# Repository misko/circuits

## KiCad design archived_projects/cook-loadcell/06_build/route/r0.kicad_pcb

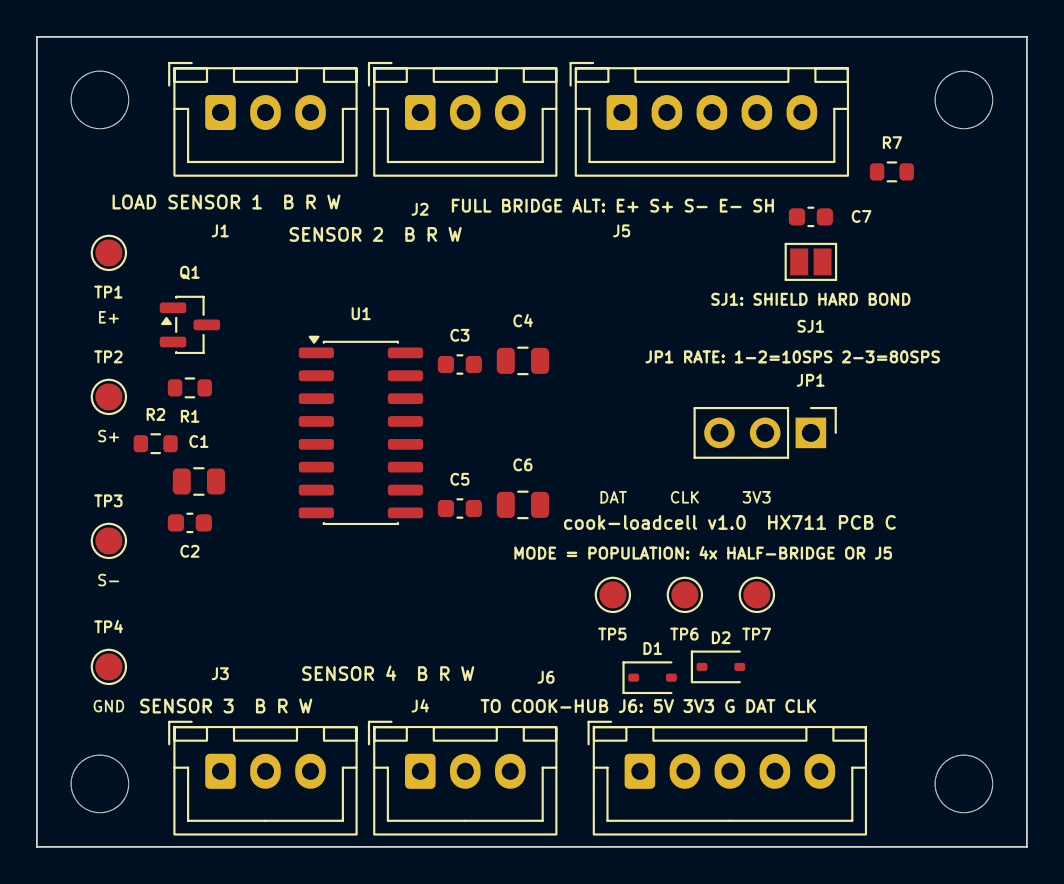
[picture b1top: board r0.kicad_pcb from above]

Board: 2 copper layers, 55.0 x 45.0 mm, 33 parts (0 on the bottom side), 16 nets, no tracks yet.

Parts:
C1: 10u E+; C_0805_2012Metric
C2: 100n E+; C_0603_1608Metric
C3: 100n DVDD; C_0603_1608Metric
C4: 10u 3V3; C_0805_2012Metric
C5: 100n VSUP; C_0603_1608Metric
C6: 10u 5V; C_0805_2012Metric
C7: 100n shield bond; C_0603_1608Metric
D1, D2: PESD5V0S1BA; D_SOD-323
H1, H2, H3, H4: MountingHole_3.2mm_M3
J1: SENSOR 1 B/R/W; JST_XH_B3B-XH-A_1x03_P2.50mm_Vertical
J2: SENSOR 2 B/R/W; JST_XH_B3B-XH-A_1x03_P2.50mm_Vertical
J3: SENSOR 3 B/R/W; JST_XH_B3B-XH-A_1x03_P2.50mm_Vertical
J4: SENSOR 4 B/R/W; JST_XH_B3B-XH-A_1x03_P2.50mm_Vertical
J5: FULL BRIDGE ALT; JST_XH_B5B-XH-A_1x05_P2.50mm_Vertical
J6: TO HUB J6; JST_XH_B5B-XH-A_1x05_P2.50mm_Vertical
JP1: RATE 1-2=10SPS 2-3=80; PinHeader_1x03_P2.54mm_Vertical
Q1: S8550; SOT-23
R1: 20k 1% AVDD-VFB; R_0603_1608Metric
R2: 8.2k 1% VFB-GND; R_0603_1608Metric
R7: 100R shield bond; R_0603_1608Metric
SJ1: SH hard bond DNP; SolderJumper-2_P1.3mm_Open_Pad1.0x1.5mm
TP1: TP E+; TestPoint_Pad_D1.5mm
TP2: TP S+; TestPoint_Pad_D1.5mm
TP3: TP S-; TestPoint_Pad_D1.5mm
TP4: TP GND; TestPoint_Pad_D1.5mm
TP5: TP DAT; TestPoint_Pad_D1.5mm
TP6: TP CLK; TestPoint_Pad_D1.5mm
TP7: TP 3V3; TestPoint_Pad_D1.5mm
U1: HX711; SOIC-16_3.9x9.9mm_P1.27mm

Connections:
3V3: C3.1, C4.1, J6.2, JP1.3, TP7.1, U1.16
5V: C5.1, C6.1, J6.1, Q1.2, U1.1
AVDD_FB: R1.2, R2.1, U1.4
BASE: Q1.1, U1.2
CLK: D2.1, J6.5, TP6.1, U1.11
DAT: D1.1, J6.4, TP5.1, U1.12
E_PLUS: C1.1, C2.1, J1.2, J5.1, Q1.3, R1.1, TP1.1, U1.3
GND: C1.2, C2.2, C3.2, C4.2, C5.2, C6.2, C7.2, D1.2, D2.2, J3.2, J5.4, J6.3, JP1.1, R2.2, R7.2, SJ1.2, TP4.1, U1.5, U1.9, U1.10, U1.14
RATE_SEL: JP1.2, U1.15
RING_12: J1.3, J2.1
RING_23: J2.3, J3.1
RING_34: J3.3, J4.1
RING_41: J1.1, J4.3
SH: C7.1, J5.5, R7.1, SJ1.1
S_MINUS: J4.2, J5.3, TP3.1, U1.7
S_PLUS: J2.2, J5.2, TP2.1, U1.8

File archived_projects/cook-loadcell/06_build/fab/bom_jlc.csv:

Comment,Designator,Footprint,MPN,LCSC
100R shield bond,R7,R_0603_1608Metric,,C22775
100n,"C2,C3,C5,C7",C_0603_1608Metric,,C14663
10u,"C1,C4,C6",C_0805_2012Metric,,C15850
20k 1% AVDD-VFB,R1,R_0603_1608Metric,,C4184
8.2k 1% VFB-GND,R2,R_0603_1608Metric,,C25981
FULL BRIDGE ALT / TO HUB J6,"J5,J6",JST_XH_B5B-XH-A_1x05_P2.50mm_Vertical,B5B-XH-A(LF)(SN),C157991
HX711,U1,SOIC-16_3.9x9.9mm_P1.27mm,,C43656
PESD5V0S1BA,"D1,D2",D_SOD-323,PESD5V0S1BA,C5158048
RATE 1-2=10SPS 2-3=80,JP1,PinHeader_1x03_P2.54mm_Vertical,,
S8550,Q1,SOT-23,SS8550,C8542
SENSOR,"J1,J2,J3,J4",JST_XH_B3B-XH-A_1x03_P2.50mm_Vertical,,C144394

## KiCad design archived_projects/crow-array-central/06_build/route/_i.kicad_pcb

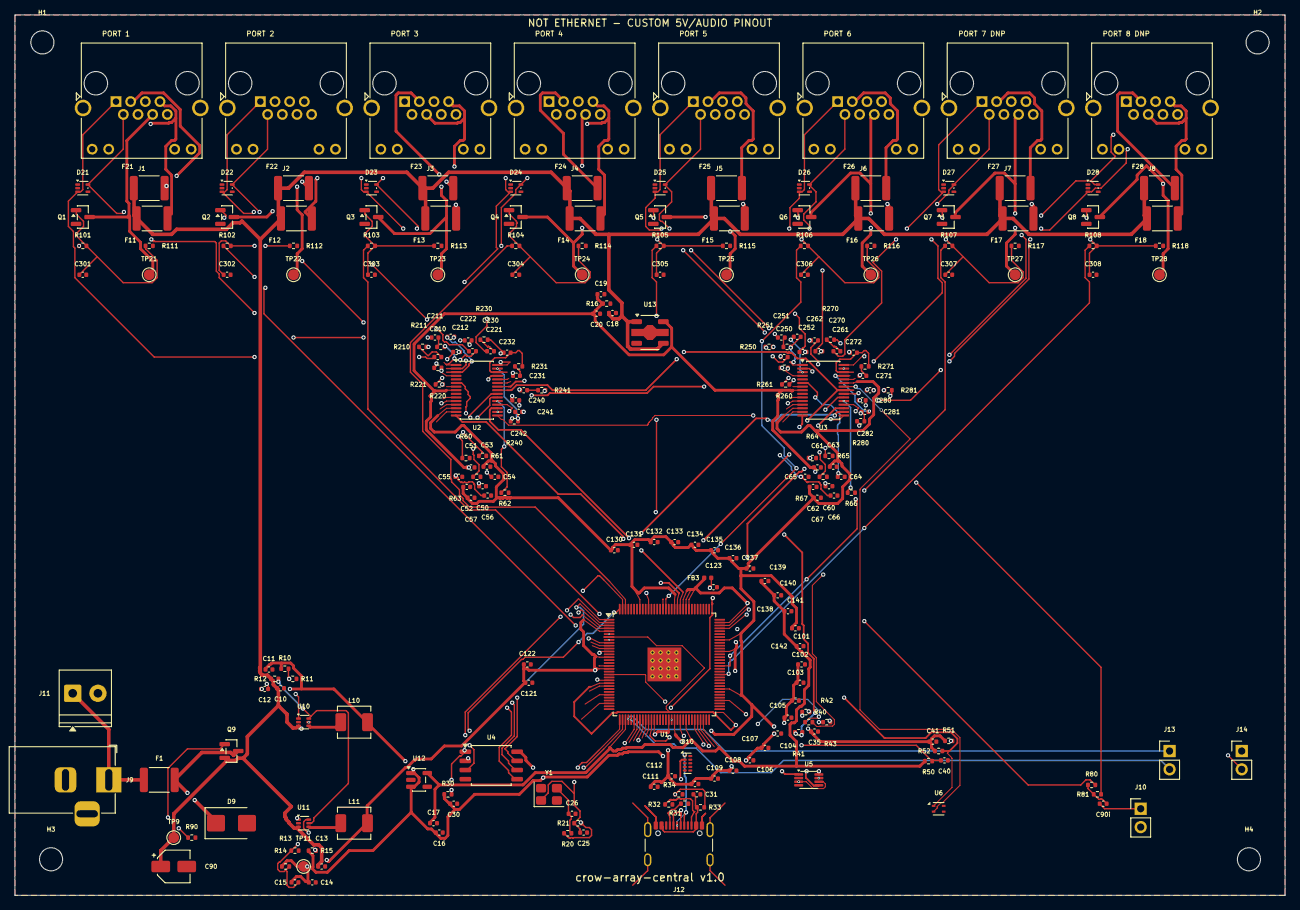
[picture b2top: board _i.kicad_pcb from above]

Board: 6 copper layers, 176.0 x 122.0 mm, 238 parts (0 on the bottom side), 151 nets.

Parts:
C10, C13, C18: 4u7 VIN; C_0402_1005Metric
C11, C136, C137: 10u 3V3; C_0402_1005Metric
C12: 100p FF; C_0402_1005Metric
C14: 22u 0V9; C_0402_1005Metric
C15: 560p FF; C_0402_1005Metric
C16: 1u VIN; C_0402_1005Metric
C17: 1u 1V8; C_0402_1005Metric
C19: 10u 3V3A; C_0402_1005Metric
C20: 100n 3V3A; C_0402_1005Metric
C25: 18p CL1; C_0402_1005Metric
C26: 18p CL2; C_0402_1005Metric
C30: 100n flash; C_0402_1005Metric
C31: 1u VBUS; C_0402_1005Metric
C35: 100n buf; C_0402_1005Metric
C40: 10n RST; C_0402_1005Metric
C41: 100n SHT; C_0402_1005Metric
C50: 4u7 AVDD_A; C_0402_1005Metric
C51: 100n AVDD_A; C_0402_1005Metric
C52: 4u7 DVDD_A; C_0402_1005Metric
C53: 100n DVDD_A; C_0402_1005Metric
C54: 2u2 VREF_A; C_0402_1005Metric
C55: 2u2 LDO_A; C_0402_1005Metric
C56: 100n LDO_A; C_0402_1005Metric
C57: 100n IOV_A; C_0402_1005Metric
C60: 4u7 AVDD_B; C_0402_1005Metric
C61: 100n AVDD_B; C_0402_1005Metric
C62: 4u7 DVDD_B; C_0402_1005Metric
C63: 100n DVDD_B; C_0402_1005Metric
C64: 2u2 VREF_B; C_0402_1005Metric
C65: 2u2 LDO_B; C_0402_1005Metric
C66: 100n LDO_B; C_0402_1005Metric
C67: 100n IOV_B; C_0402_1005Metric
C90: 100u 5V bulk; CP_Elec_4x5.4
C90i: 1u inj; C_0402_1005Metric
C101, C102, C103, C104, C105, C106, C107, C108, C109, C110, C111, C112: 100n VDD; C_0402_1005Metric
C121, C122: 10u VDD; C_0402_1005Metric
C123: 1u PLL; C_0402_1005Metric
C130, C131, C132, C133, C134, C135: 100n 3V3; C_0402_1005Metric
C138, C139: 100n 1V8; C_0402_1005Metric
C140: 10u 1V8; C_0402_1005Metric
C141: 100n USB33; C_0402_1005Metric
C142: 100n USB18; C_0402_1005Metric
C210: 1u cpl P1; C_0402_1005Metric
C211: 1u cpl N1; C_0402_1005Metric
C212: 1n diff 1; C_0402_1005Metric
C220: 1u cpl P2; C_0402_1005Metric
C221: 1u cpl N2; C_0402_1005Metric
C222: 1n diff 2; C_0402_1005Metric
C230: 1u cpl P3; C_0402_1005Metric
C231: 1u cpl N3; C_0402_1005Metric
C232: 1n diff 3; C_0402_1005Metric
C240: 1u cpl P4; C_0402_1005Metric
C241: 1u cpl N4; C_0402_1005Metric
C242: 1n diff 4; C_0402_1005Metric
C250: 1u cpl P5; C_0402_1005Metric
C251: 1u cpl N5; C_0402_1005Metric
C252: 1n diff 5; C_0402_1005Metric
C260: 1u cpl P6; C_0402_1005Metric
C261: 1u cpl N6; C_0402_1005Metric
C262: 1n diff 6; C_0402_1005Metric
C270: 1u cpl P7; C_0402_1005Metric
C271: 1u cpl N7; C_0402_1005Metric
C272: 1n diff 7; C_0402_1005Metric
C280: 1u cpl P8; C_0402_1005Metric
C281: 1u cpl N8; C_0402_1005Metric
C282: 1n diff 8; C_0402_1005Metric
C301: 4n7 gate 1; C_0402_1005Metric
C302: 4n7 gate 2; C_0402_1005Metric
C303: 4n7 gate 3; C_0402_1005Metric
C304: 4n7 gate 4; C_0402_1005Metric
C305: 4n7 gate 5; C_0402_1005Metric
C306: 4n7 gate 6; C_0402_1005Metric
C307: 4n7 gate 7; C_0402_1005Metric
C308: 4n7 gate 8; C_0402_1005Metric
D9: SMBJ5.0A TVS; D_SMB
D10: TPD4EUSB30; USON-10_2.5x1.0mm_P0.5mm
D21: TPD2E2U06 p1; SOT-553
D22: TPD2E2U06 p2; SOT-553
D23: TPD2E2U06 p3; SOT-553
D24: TPD2E2U06 p4; SOT-553
D25: TPD2E2U06 p5; SOT-553
D26: TPD2E2U06 p6; SOT-553
D27: TPD2E2U06 p7; SOT-553
D28: TPD2E2U06 p8; SOT-553
F1: 2A PTC; Fuse_1812_4532Metric
F11: PTC audio 1; Fuse_1812_4532Metric
F12: PTC audio 2; Fuse_1812_4532Metric
F13: PTC audio 3; Fuse_1812_4532Metric
F14: PTC audio 4; Fuse_1812_4532Metric
F15: PTC audio 5; Fuse_1812_4532Metric
F16: PTC audio 6; Fuse_1812_4532Metric
F17: PTC audio 7; Fuse_1812_4532Metric
F18: PTC audio 8; Fuse_1812_4532Metric
F21: PTC beep 1; Fuse_1812_4532Metric
F22: PTC beep 2; Fuse_1812_4532Metric
F23: PTC beep 3; Fuse_1812_4532Metric
F24: PTC beep 4; Fuse_1812_4532Metric
F25: PTC beep 5; Fuse_1812_4532Metric
F26: PTC beep 6; Fuse_1812_4532Metric
F27: PTC beep 7; Fuse_1812_4532Metric
F28: PTC beep 8; Fuse_1812_4532Metric
FB3: 600R PLL; L_0402_1005Metric
H1, H2, H3, H4: MountingHole_3.2mm_M3
J1, J2, J3, J4, J5, J6: RJHSE-5384; RJ45_Amphenol_RJHSE538X
J7, J8: RJHSE-5384 DNP; RJ45_Amphenol_RJHSE538X
J9: DC-005 5V IN; BarrelJack_Horizontal
J10: INJ IN; PinHeader_1x02_P2.54mm_Vertical
J11: 5V TERM DNP; TerminalBlock_Phoenix_PT-1,5-2-3.5-H_1x02_P3.50mm_Horizontal
J12: USB4105-GF-A; USB_C_Receptacle_GCT_USB4105-xx-A_16P_TopMnt_Horizontal
J13: xSYS DBG TDI/TDO; PinHeader_1x02_P2.54mm_Vertical
J14: xSYS DBG TMS/TCK; PinHeader_1x02_P2.54mm_Vertical
L10: 1u0 3V3; L_Sunlord_MWSA0402S
L11: 1u0 0V9; L_Sunlord_MWSA0402S
Q1: AO3400A beep 1; SOT-23
Q2: AO3400A beep 2; SOT-23
Q3: AO3400A beep 3; SOT-23
Q4: AO3400A beep 4; SOT-23
Q5: AO3400A beep 5; SOT-23
Q6: AO3400A beep 6; SOT-23
Q7: AO3400A beep 7; SOT-23
Q8: AO3400A beep 8; SOT-23
Q9: AO3401A revFET; SOT-23
R10: 68k FB1 hi; R_0402_1005Metric
R11: 15k FB1 lo; R_0402_1005Metric
R12: 10k PG1 pu; R_0402_1005Metric
R13: 10k FB2 hi; R_0402_1005Metric
R14: 20k FB2 lo; R_0402_1005Metric
R15: 10k PG2 pu; R_0402_1005Metric
R16: 4k7 bleed; R_0402_1005Metric
R20: 680R Rd; R_0402_1005Metric
R21: 1M Rf; R_0402_1005Metric
R30: 10k CS pu; R_0402_1005Metric
R31: 5k1 CC1 Rd; R_0402_1005Metric
R32: 5k1 CC2 Rd; R_0402_1005Metric
R33: 220k VBUS; R_0402_1005Metric
R34: 330k VBUS; R_0402_1005Metric
R40: 33R MCLK_A; R_0402_1005Metric
R41: 33R MCLK_B; R_0402_1005Metric
R42: 33R BCLK; R_0402_1005Metric
R43: 33R LRCK; R_0402_1005Metric
R50: 10k RST pu; R_0402_1005Metric
R51: 4k7 SCL pu; R_0402_1005Metric
R52: 4k7 SDA pu; R_0402_1005Metric
R60: 100k GP0_A; R_0402_1005Metric
R61: 100k GP1_A; R_0402_1005Metric
R62: 100k GP2_A; R_0402_1005Metric
R63: 100k GP3_A; R_0402_1005Metric
R64: 100k GP0_B; R_0402_1005Metric
R65: 100k GP1_B; R_0402_1005Metric
R66: 100k GP2_B; R_0402_1005Metric
R67: 100k GP3_B; R_0402_1005Metric
R80: 1k inj ch4; R_0402_1005Metric
R81: 1k inj ch8; R_0402_1005Metric
R90: 100k FET gate; R_0402_1005Metric
R101: 1k gate 1; R_0402_1005Metric
R102: 1k gate 2; R_0402_1005Metric
R103: 1k gate 3; R_0402_1005Metric
R104: 1k gate 4; R_0402_1005Metric
R105: 1k gate 5; R_0402_1005Metric
R106: 1k gate 6; R_0402_1005Metric
R107: 1k gate 7; R_0402_1005Metric
R108: 1k gate 8; R_0402_1005Metric
R111: 100k pd 1; R_0402_1005Metric
R112: 100k pd 2; R_0402_1005Metric
R113: 100k pd 3; R_0402_1005Metric
R114: 100k pd 4; R_0402_1005Metric
R115: 100k pd 5; R_0402_1005Metric
R116: 100k pd 6; R_0402_1005Metric
R117: 100k pd 7; R_0402_1005Metric
R118: 100k pd 8; R_0402_1005Metric
R210: 49R9 P1; R_0402_1005Metric
R211: 49R9 N1; R_0402_1005Metric
R220: 49R9 P2; R_0402_1005Metric
R221: 49R9 N2; R_0402_1005Metric
R230: 49R9 P3; R_0402_1005Metric
R231: 49R9 N3; R_0402_1005Metric
R240: 49R9 P4; R_0402_1005Metric
R241: 49R9 N4; R_0402_1005Metric
R250: 49R9 P5; R_0402_1005Metric
R251: 49R9 N5; R_0402_1005Metric
R260: 49R9 P6; R_0402_1005Metric
R261: 49R9 N6; R_0402_1005Metric
R270: 49R9 P7; R_0402_1005Metric
R271: 49R9 N7; R_0402_1005Metric
R280: 49R9 P8; R_0402_1005Metric
R281: 49R9 N8; R_0402_1005Metric
TP9: TP 5V; TestPoint_Pad_D1.5mm
TP11: TP 0V9; TestPoint_Pad_D1.5mm
TP21: TP BEEP_RET1; TestPoint_Pad_D1.5mm
TP22: TP BEEP_RET2; TestPoint_Pad_D1.5mm
TP23: TP BEEP_RET3; TestPoint_Pad_D1.5mm
TP24: TP BEEP_RET4; TestPoint_Pad_D1.5mm
TP25: TP BEEP_RET5; TestPoint_Pad_D1.5mm
TP26: TP BEEP_RET6; TestPoint_Pad_D1.5mm
TP27: TP BEEP_RET7; TestPoint_Pad_D1.5mm
TP28: TP BEEP_RET8; TestPoint_Pad_D1.5mm
U1: XU316-1024-TQ128-I24; TQFP-128_14x14mm_P0.4mm_EP4.7mm
U2, U3: PCM1865DBTR; TSSOP-30_4.4x7.8mm_P0.5mm
U4: W25Q16JVSSIQ; SOIC-8_5.3x5.3mm_P1.27mm
U5: NC7NZ34 MCLK buf; VSSOP-8_2.3x2mm_P0.5mm
U6: SHT40-AD1B (0x44); Sensirion_DFN-4_1.5x1.5mm_P0.8mm_SHT4x_NoCentralPad
U10: AP61102 3V3; SOT-563
U11: AP61102 0V9; SOT-563
U12: TCR2LF18 1V8; SOT-23-5
U13: XC6227 3V3A; SOT-89-5
Y1: FA-238 24MHz; Crystal_SMD_3225-4Pin_3.2x2.5mm

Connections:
0V9: C14.1, C15.1, C101.1, C102.1, C103.1, C104.1, C105.1, C106.1, C107.1, C108.1, C109.1, C110.1, C111.1, C112.1, C121.1, C122.1, FB3.1, L11.2, R13.1, TP11.1, U1.5, U1.11, U1.14, U1.18, U1.39, U1.45, U1.50, U1.54, U1.68, U1.85, U1.95, U1.104, U1.105, U1.106, U1.113
1V8: C17.1, C138.1, C139.1, C140.1, C142.1, R50.1, U1.35, U1.56, U1.62, U12.5
3V3: C11.1, C12.1, C16.1, C30.1, C35.1, C41.1, C52.1, C53.1, C57.1, C62.1, C63.1, C67.1, C130.1, C131.1, C132.1, C133.1, C134.1, C135.1, C136.1, C137.1, C141.1, L10.2, R10.1, R15.1, R30.1, R51.1, R52.1, U1.10, U1.17, U1.40, U1.43, U1.52, U1.61, U1.72, U1.89, U1.109, U1.121, U2.13, U2.14, U3.13, U3.14, U3.25, U4.8, U5.8, U6.3, U12.1, U12.3
3V3A: C19.1, C20.1, C50.1, C51.1, C60.1, C61.1, R16.1, U2.8, U3.8, U13.5
5V: C10.1, C13.1, C18.1, C90.1, F11.1, F12.1, F13.1, F14.1, F15.1, F16.1, F17.1, F18.1, F21.1, F22.1, F23.1, F24.1, F25.1, F26.1, F27.1, F28.1, Q9.2, R12.1, TP9.1, U10.3, U10.5, U11.3, U13.1, U13.4
5V_AUD1: F11.2, J1.4, J1.7
5V_AUD2: F12.2, J2.4, J2.7
5V_AUD3: F13.2, J3.4, J3.7
5V_AUD4: F14.2, J4.4, J4.7
5V_AUD5: F15.2, J5.4, J5.7
5V_AUD6: F16.2, J6.4, J6.7
5V_AUD7: F17.2, J7.4, J7.7
5V_AUD8: F18.2, J8.4, J8.7
5V_IN: F1.1, J9.1, J11.1
5V_P: D9.1, F1.2, Q9.3
AIN_N1: C211.2, R211.1
AIN_N2: C221.2, R221.1
AIN_N3: C231.2, R231.1
AIN_N4: C241.2, R241.1
AIN_N5: C251.2, R251.1
AIN_N6: C261.2, R261.1
AIN_N7: C271.2, R271.1
AIN_N8: C281.2, R281.1
AIN_P1: C210.2, R210.1
AIN_P2: C220.2, R220.1
AIN_P3: C230.2, R230.1
AIN_P4: C240.2, R80.2, R240.1
AIN_P5: C250.2, R250.1
AIN_P6: C260.2, R260.1
AIN_P7: C270.2, R270.1
AIN_P8: C280.2, R81.2, R280.1
AUD_N1: C211.1, D21.5, J1.2
AUD_N2: C221.1, D22.5, J2.2
AUD_N3: C231.1, D23.5, J3.2
AUD_N4: C241.1, D24.5, J4.2
AUD_N5: C251.1, D25.5, J5.2
AUD_N6: C261.1, D26.5, J6.2
AUD_N7: C271.1, D27.5, J7.2
AUD_N8: C281.1, D28.5, J8.2
AUD_P1: C210.1, D21.3, J1.1
AUD_P2: C220.1, D22.3, J2.1
AUD_P3: C230.1, D23.3, J3.1
AUD_P4: C240.1, D24.3, J4.1
AUD_P5: C250.1, D25.3, J5.1
AUD_P6: C260.1, D26.3, J6.1
AUD_P7: C270.1, D27.3, J7.1
AUD_P8: C280.1, D28.3, J8.1
BCLK: R42.2, U2.17, U3.17
BCLK_X: R42.1, U1.22
BEEP_5V1: F21.2, J1.3
BEEP_5V2: F22.2, J2.3
BEEP_5V3: F23.2, J3.3
BEEP_5V4: F24.2, J4.3
BEEP_5V5: F25.2, J5.3
BEEP_5V6: F26.2, J6.3
BEEP_5V7: F27.2, J7.3
BEEP_5V8: F28.2, J8.3
BEEP_G1: R101.1, U1.6
BEEP_G2: R102.1, U1.9
BEEP_G3: R103.1, U1.12
BEEP_G4: R104.1, U1.126
BEEP_G5: R105.1, U1.118
BEEP_G6: R106.1, U1.112
BEEP_G7: R107.1, U1.80
BEEP_G8: R108.1, U1.77
BEEP_RET1: J1.6, Q1.3, TP21.1
BEEP_RET2: J2.6, Q2.3, TP22.1
BEEP_RET3: J3.6, Q3.3, TP23.1
BEEP_RET4: J4.6, Q4.3, TP24.1
BEEP_RET5: J5.6, Q5.3, TP25.1
BEEP_RET6: J6.6, Q6.3, TP26.1
BEEP_RET7: J7.6, Q7.3, TP27.1
BEEP_RET8: J8.6, Q8.3, TP28.1
BG_1: C301.1, Q1.1, R101.2, R111.1
BG_2: C302.1, Q2.1, R102.2, R112.1
BG_3: C303.1, Q3.1, R103.2, R113.1
BG_4: C304.1, Q4.1, R104.2, R114.1
BG_5: C305.1, Q5.1, R105.2, R115.1
BG_6: C306.1, Q6.1, R106.2, R116.1
BG_7: C307.1, Q7.1, R107.2, R117.1
BG_8: C308.1, Q8.1, R108.2, R118.1
BK1_PG: R12.2, U10.6, U11.5
BK1_SW: L10.1, U10.4
BK2_PG: R15.2, U11.6
BK2_SW: L11.1, U11.4
CC1: J12.A5, R31.1
CC2: J12.B5, R32.1
DATA1: U1.107, U2.18
DATA2: U1.108, U3.18
FB1: C12.2, R10.2, R11.1, U10.1
FB2: C15.2, R13.2, R14.1, U11.1
GATE9: Q9.1, R90.1
GND: C10.2, C11.2, C13.2, C14.2, C16.2, C17.2, C18.2, C19.2, C20.2, C25.2, C26.2, C30.2, C31.2, C35.2, C40.2, C41.2, C50.2, C51.2, C52.2, C53.2, C54.2, C55.2, C56.2, C57.2, C60.2, C61.2, C62.2, C63.2, C64.2, C65.2, C66.2, C67.2, C90.2, C101.2, C102.2, C103.2, C104.2, C105.2, C106.2, C107.2, C108.2, C109.2, C110.2, C111.2, C112.2, C121.2, C122.2, C123.2, C130.2, C131.2, C132.2, C133.2, C134.2, C135.2, C136.2, C137.2, C138.2, C139.2, C140.2, C141.2, C142.2, C301.2, C302.2, C303.2, C304.2, C305.2, C306.2, C307.2, C308.2, D9.2, D10.3, D10.8, D21.4, D22.4, D23.4, D24.4, D25.4, D26.4, D27.4, D28.4, J1.5, J1.8, J1.SH, J2.5, J2.8, J2.SH, J3.5, J3.8, J3.SH, J4.5, J4.8, J4.SH, J5.5, J5.8, J5.SH, J6.5, J6.8, J6.SH, J7.5, J7.8, J7.SH, J8.5, J8.8, J8.SH, J9.2, J9.3, J10.2, J11.2, J12.A1, J12.A12, J12.B1, J12.B12, J12.SH, Q1.2, Q2.2, Q3.2, Q4.2, Q5.2, Q6.2, Q7.2, Q8.2, R11.2, R14.2, R16.2, R31.2, R32.2, R34.2, R60.2, R61.2, R62.2, R63.2, R64.2, R65.2, R66.2, R67.2, R90.2, R111.2, R112.2, R113.2, R114.2, R115.2, R116.2, R117.2, R118.2, U1.24, U1.27, U1.30, U1.42, U1.129, U2.7, U2.10, U2.12, U2.25, U2.26, U3.7, U3.10, U3.12, U3.26, U4.4, U5.4, U6.4, U10.2, U11.2, U12.2, U13.2, Y1.2, Y1.4
GP0_A: R60.1, U2.22
GP0_B: R64.1, U3.22
GP1_A: R61.1, U2.21
GP1_B: R65.1, U3.21
GP2_A: R62.1, U2.20
GP2_B: R66.1, U3.20
GP3_A: R63.1, U2.19
GP3_B: R67.1, U3.19
I2C_SCL: R51.2, U1.93, U2.24, U3.24, U6.2
I2C_SDA: R52.2, U1.94, U2.23, U3.23, U6.1
INJ: C90i.1, J10.1
INJ_C: C90i.2, R80.1, R81.1
LDO_A: C55.1, C56.1, U2.11
LDO_B: C65.1, C66.1, U3.11
LRCK: R43.2, U2.16, U3.16
LRCK_X: R43.1, U1.20
MCLK_A: R40.2, U2.15
MCLK_A0: R40.1, U5.7
MCLK_B: R41.2, U3.15
MCLK_B0: R41.1, U5.5
MCLK_SRC: U1.7, U1.23, U5.1, U5.3, U5.6
PLL_AVDD: C123.1, FB3.2, U1.41
QSPI_CLK: U1.4, U4.6
QSPI_CS: R30.2, U1.2, U4.1
QSPI_D0: U1.127, U4.5
QSPI_D1: U1.128, U4.2
QSPI_D2: U1.1, U4.3
QSPI_D3: U1.3, U4.7
RST_N: C40.1, R50.2, U1.38
TCK: J14.2, U1.51
TDI: J13.1, U1.36
TDO: J13.2, U1.37
TMS: J14.1, U1.44
USB_DM: D10.2, J12.A7, J12.B7, U1.59
USB_DP: D10.1, J12.A6, J12.B6, U1.60
VA1M: C212.2, R211.2, U2.1
VA1P: C212.1, R210.2, U2.3
VA2M: C222.2, R221.2, U2.2
VA2P: C222.1, R220.2, U2.4
VA3M: C232.2, R231.2, U2.28
VA3P: C232.1, R230.2, U2.30
VA4M: C242.2, R241.2, U2.27
VA4P: C242.1, R240.2, U2.29
VB1M: C252.2, R251.2, U3.1
VB1P: C252.1, R250.2, U3.3
VB2M: C262.2, R261.2, U3.2
VB2P: C262.1, R260.2, U3.4
VB3M: C272.2, R271.2, U3.28
VB3P: C272.1, R270.2, U3.30
VB4M: C282.2, R281.2, U3.27
VB4P: C282.1, R280.2, U3.29
VBUS: C31.1, J12.A4, J12.A9, J12.B4, J12.B9, R33.1
VBUS_DET: R33.2, R34.1, U1.8
VREF_A: C54.1, U2.6
VREF_B: C64.1, U3.6
XIN: C25.1, R21.1, U1.34, Y1.1
XOUT: R20.1, R21.2, U1.33
XTAL2: C26.1, R20.2, Y1.3
